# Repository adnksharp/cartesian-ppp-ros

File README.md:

# Cartesian Robot (PPP) ROS2

Robot cartesiano de 3 DOF con ROS2,

## Software y Hardware

<details>
    <summary>Software</summary>

* [ROS2 Jazzy](https://index.ros.org/p/desktop_full/#jazzy)
* [Gazebo Harmonic](https://gazebosim.org/docs/harmonic/getstarted/)
* [uROS Jazzy](https://github.com/micro-ROS/micro_ros_setup/tree/jazzy)
* [uROS Arduino Jazzy](https://github.com/micro-ROS/micro_ros_arduino/tree/jazzy)
* [KiCad](https://www.kicad.org)

</details>

<details>
    <summary>Componentes electrónicos</summary>

* 1 [ESP32 S3 WROOM 1 N16R8 DevKit](https://www.amazon.com/HiLetgo-ESP32-S3-ESP32-S3-DevKit-Bluetooth-Development/dp/B0CDWXWXCG)
* 2 [Módulos controladores de motores L298N](https://www.amazon.com/WWZMDiB-L298N-H-Bridge-Controller-Raspberry/dp/B0CR6BX5QL)
* 3 [Motores con encoder JGA25-371](https://www.amazon.com/JGA25-371-Encoder-Mounting-Bracket-Reduction/dp/B0CGLSGSZ7)
* 4 [LEDs 5730](https://www.amazon.com/AEDIKO-Lighting-Electronics-Components-Emitting/dp/B09XB5KDWS)
* 4 [Resistencias 220 Ohms 1206](https://www.amazon.com/Chanzon-Resistor-Tolerance-Resistors-Certificated/dp/B08R8CW7TX)
* 1 Fuente de alimentación 12V 2A

</details>

<details>
    <summary>Componentes mecánicos</summary>

* 12 perfiles de aluminio de 45x45x300 mm.
* 16 ángulos de aluminio de 45x45 mm.
* 3 tuercas de latón T8.
* 3 tornillos sin fin de 8x300 mm.
* 3 varillas lisas de 8x300 mm.
* 3 rodamientos SC8UU.
* 3 acopladores flexibles de 5x8 mm.
* 5 chumaceras KP08.
* 6 soportes SK8.
* Piezas impresas en 3D.

</details>

## Instalación
Para instalar el software de ROS2 Jazzy, se recomienda seguir la guía oficial de instalación de [ROS2](https://docs.ros.org/en/jazzy/Installation/Ubuntu-Install-Debs.html), el siguiente script instala el software de ROS2, Gazebo sim y micro-ROS en Ubuntu:

```shell
$SHELL ./src/install-ros.sh
```

Más información sobre el script en [src](src).

## Espacio de Trabajo de ROS2
Dentro de la carpeta ros-ws se encuentra el paquete en desarrollo `carobot`, el cual contiene los archivos para la visualización y simulación del robot cartesiano en Gazebo y RViz.

### Construcción del espacio de trabajo

```shell
cd ros-ws
colcon build
```

### Ejecución del lanzador

```shell
source install/setup.$(echo $SHELL | awk -F '/' '{print $NF}')
ros2 launch carobot display.launch.py
```

### Ejecución de la interfaz de usuario

```shell
source install/setup.$(echo $SHELL | awk -F '/' '{print $NF}')
ros2 run carobot pos_put.py
```

[ros-ws](ros-ws) contiene más información sobre el espacio de trabajo de ROS2.

## Electrónica

[electronic](electronic) contiene el diseño de la PCB del robot cartesiano en formato KiCad, el cual incluye el diseño de la PCB y el esquema eléctrico.

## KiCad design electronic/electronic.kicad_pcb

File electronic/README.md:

# Esquema elctrónico

El proyecto se desarrolló usando [KiCAD](https://www.kicad.org/). ([electronic.kicad_pro](electronic.kicad_pro)) se desarrollo para conectar una placa de ESP32 con 2 controladores de motores L298 y encoders de 3 motores JGA25-371. Los componentes utilizados en el proyecto son:

* 1 **ESP32 S3** WROOM 1 N16R8 DevKit
* 2 Modulos controladores de motores **L298**
* 3 Motores con encoder **JGA25-371**
* 4 LEDs
* 4 Resistencias **220 $\Omega$**
* 1 Fuente de alimentación **12V 2A**

## Esquema

El esquema eléctrico se encuentra dividido en ocho partes:

* 1 Alimentación: En esta sección se encuentra el conector de la fuente de alimentación para el circuito.
* 3 Motores
* 1 LED: LEDS conectados a los pines GPIO del microcontrolador y resistencias de 220 $\Omega$.
* 2 Controladores de motores
* 1 Microcontrolador

### Motores
En esta sección se encuentran los motores con encoder **JGA25-371**. 

* Las etiquetas del encoder se conectan a los pines GPIO del microcontrolador.
* Las etiquetas de alimentación se conectan a la salida de 3.3V del microcontrolador.
* Las etiquetas de los motores se conectan a los controladores de motores.

### Controladores de motores
En esta sección se encuentran los módulos de controladores de motores **L298N**. 

* Las etiquetas de los pines de control de los módulos se conectan a los pines GPIO del microcontrolador.
* Las etiquetas de alimentación se conectan a la fuente de alimentación y la salida de 5V de los controladores a la alimentación del microcontrolador.
* Las etiquetas de los motores se conectan a los motores.

### Microcontrolador
En esta sección se encuentra el microcontrolador **ESP32 S3** y las etiquetas de los pines que se utilizan para la comunicación con el resto de los componentes.

## PCB

La PCB fue diseñada para conectar todos los componentes del circuito. La PCB tiene un tamaño de 68.5x75 mm y fue diseñada para ser fabricada en dos capas. El diseño se encuentra en la carpeta `electronic` ([PCB.kicad_pcb](PCB.kicad_pcb)). Para la PCB se usan los siguientes componentes:

* 1 PCB de dos capas
* 1 Conector de alimentación **Barrel Jack**
* 2 Conectores **JST-B3B** para la alimentación de los controladores de motores.
* 3 Conectores **JST-B4B** para la conexión de los encoders de los motores.
* 2 Conectores **JST-B5B** para la conexión de los pines de control de los controladores de motores.
* 1 Terminal de 44 pines para la conexión del microcontrolador.
* 4 LEDs SMD **5730**
* 4 Resistencias 220 $\Omega$ SMD **1206**

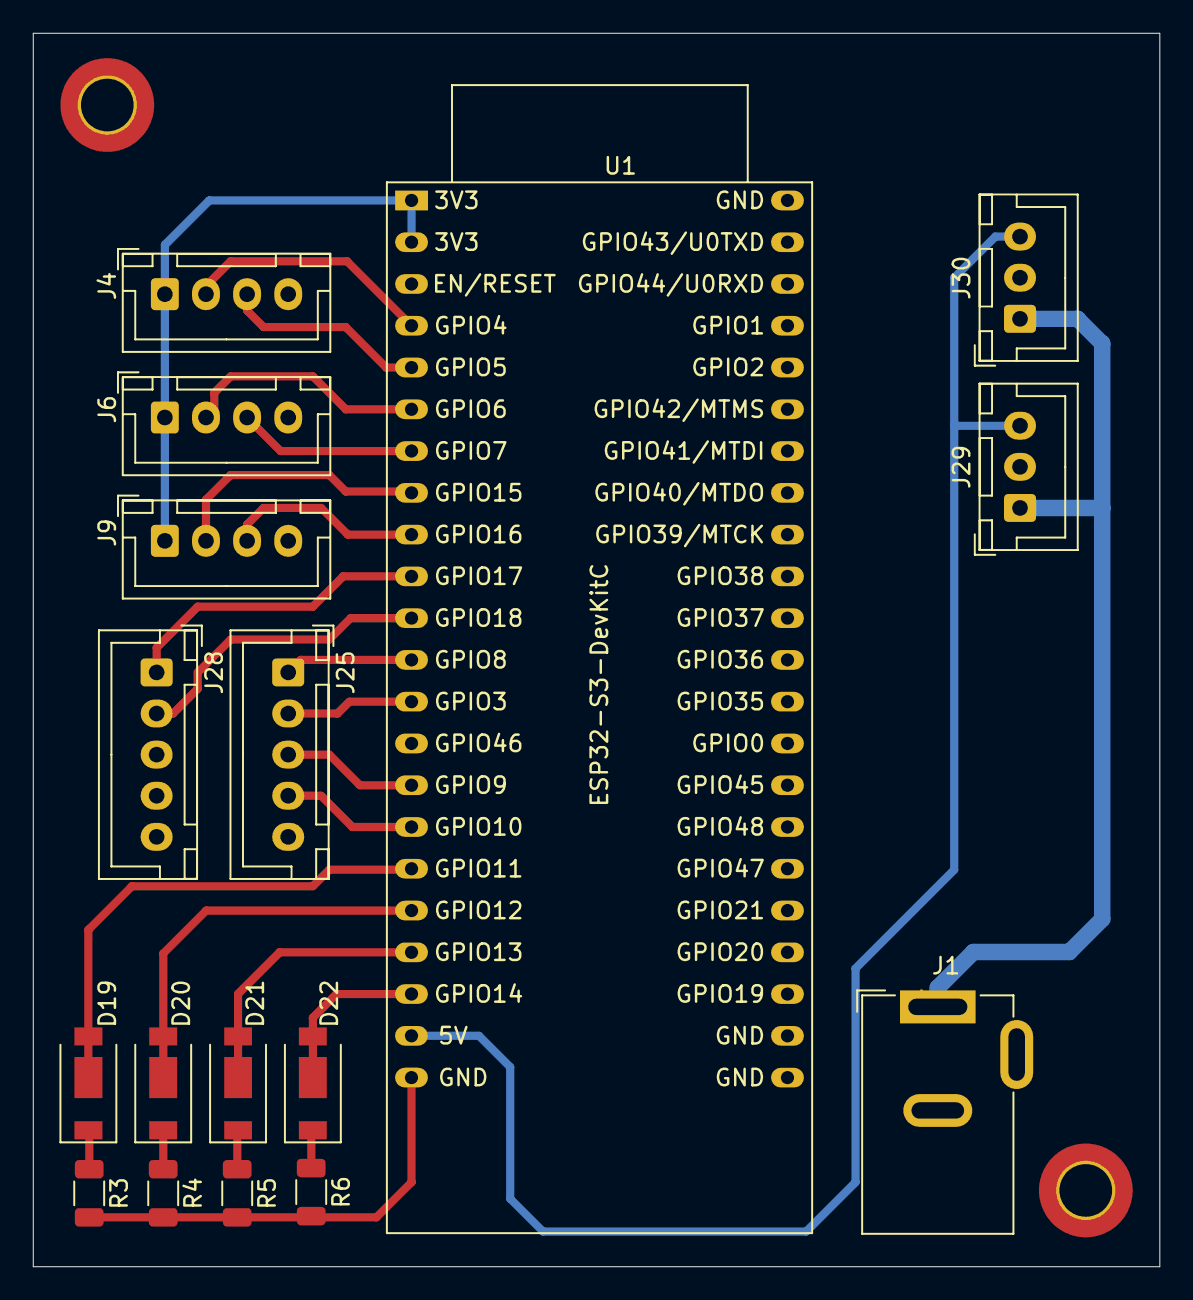
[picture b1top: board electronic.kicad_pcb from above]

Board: 2 copper layers, 68.5 x 75.0 mm, 17 parts (0 on the bottom side), 24 nets.

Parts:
D19, D20, D21, D22: LED; LED_Yuji_5730
J1: POWER SUPLY; BarrelJack_GCT_DCJ200-10-A_Horizontal
J4: ENC01; JST_XH_B4B-XH-A_1x04_P2.50mm_Vertical
J6: ENC02; JST_XH_B4B-XH-A_1x04_P2.50mm_Vertical
J9: ENC03; JST_XH_B4B-XH-A_1x04_P2.50mm_Vertical
J25, J28: Conn_01x05; JST_XH_B5B-XH-A_1x05_P2.50mm_Vertical
J29, J30: Screw_Terminal_01x03; JST_XH_B3B-XH-A_1x03_P2.50mm_Vertical
R3, R4, R5, R6: 220; R_1206_3216Metric
U1: ESP32-S3-DevKitC

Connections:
+3.3V: J4.1, J6.1, J9.1, U1.1 (3V3), U1.2 (3V3)
+5V: J29.3, J30.3, U1.21 (5V)
+12V: J1.1, J29.1, J30.1
DRVI101: J25.1, U1.12 (GPIO8/ADC1_CH7)
DRVI102: J28.1, U1.10 (GPIO17/ADC2_CH6)
DRVI201: J25.2, U1.13 (GPIO3/ADC1_CH2)
DRVI202: J28.2, U1.11 (GPIO18/ADC2_CH7)
DRVI301: J25.3, U1.15 (GPIO9/ADC1_CH8)
DRVI401: J25.4, U1.16 (GPIO10/ADC1_CH9)
Earth: J1.2, J4.4, J6.4, J9.4, J25.5, J28.5, J29.2, J30.2, R3.2, R4.2, R5.2, R6.2, U1.22 (GND), U1.23 (GND), U1.24 (GND), U1.44 (GND)
L_ENC_1: D19.2 (A), U1.17 (GPIO11/ADC2_CH0)
L_ENC_2: D20.2 (A), U1.18 (GPIO12/ADC2_CH1)
L_ENC_3: D21.2 (A), U1.19 (GPIO13/ADC2_CH2)
L_ROS: D22.2 (A), U1.20 (GPIO14/ADC2_CH3)
unnamed: D19.1 (K), R3.1
unnamed: D20.1 (K), R4.1
unnamed: D21.1 (K), R5.1
unnamed: D22.1 (K), R6.1
PH_A01: J4.2, U1.4 (GPIO4/ADC1_CH3)
PH_A02: J6.2, U1.6 (GPIO6/ADC1_CH5)
PH_A03: J9.2, U1.8 (GPIO15/ADC2_CH4/32K_P)
PH_B01: J4.3, U1.5 (GPIO5/ADC1_CH4)
PH_B02: J6.3, U1.7 (GPIO7/ADC1_CH6)
PH_B03: J9.3, U1.9 (GPIO16/ADC2_CH5/32K_N)

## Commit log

2025-03-03 chore: ros workspace init
2025-03-03 chore: ros workspace added to .gitignore
2025-03-10 chore: .gitignore updated
2025-03-13 test: uROS encoder publish topics
2025-03-13 chore: JGA MOTORS and L298N drivers added to KiCadschematic
2025-03-13 chore: pcd made
2025-03-13 chore: PCB updated
2025-03-13 chore: gerbar and images added
2025-03-13 chore: M3 hole added to PCB
2025-03-13 chore: images updated
2025-03-13 chore: gerber updated
2025-03-13 chore: 3d files updated
2025-03-14 chore: missing 3D models added to PCB
2025-03-14 chore: 3D model of L298N driver module added to the project
2025-03-14 chore: STL and STEP PCB files updated
2025-03-15 refactor: src dir changed
2025-03-15 chore: PCB Lite design added to the project
2025-03-18 docs: update README.md
2025-03-22 refactor (electronic): update PCB design
2025-03-24 chore (PCB 3D.png): update img files
2025-03-24 feat(ros-ws): start urdf project, publish robot with ROS2 and gazebo
2025-03-24 refactor(aunch/gazebo.launch.py): delete model path
2025-03-25 style(model.urdf): add colors to links
2025-03-28 chore(carobot): rename *_*.STL files to *.STL and add launcher for display the project in rviz2
2025-03-31 fix(model.urdf): coorect position and limit of joints and links in the model
2025-03-31 Revert "fix(model.urdf): coorect position and limit of joints and links in the model"
    This reverts commit 3ffb0695d2ab54cb5759cbb24cd0175b31b29e9f.
2025-03-31 Reapply "fix(model.urdf): coorect position and limit of joints and links in the model"
    This reverts commit d187cfb64390a7ce33d66d2385a874b4d395dfab.
2025-03-31 fix(model.urdf): correct position and limit of joints and links in the model
2025-03-31 fix(display.launch.py): add gui options for /opt/ros/jazzy/share/urdf_launch/launch/display.launch.py modified script
2025-04-05 feat(ros-ws/carobot): publish joint status from ROS2 (joint_state_publisher_gui) to gz by ros_gz_bridge
2025-04-06 fix(model.urdf): correct some definitions
2025-04-06 chore(model.urdf): test pid configurations
2025-04-06 refactor (img): update images
2025-04-07 chore(ros-ws): edit model.urdf
2025-04-09 refactor(ros-ws): update joint_state publisher based in data of gz sim
2025-04-11 refactor(ros-ws): change the filename attrib in urdf to use relative directory based on the project
2025-04-15 chore(stl): update STL files for the new design
2025-04-16 fix(model.urdf): update meshes and limits for new stl files
2025-04-16 chore (img): add Gazebo and RViz2 screenshots
2025-04-16 refactor(src): add scripts for install ROS2 and Gazebo sim
2025-04-16 chore(src): uncomment commands on install scripts
2025-04-17 feat(install-ros.sh): add micro-ROS install commands
2025-04-17 docs (README.md): update markdown files
2025-04-18 chore(electronic): update kicad files
2025-04-20 fix(carobot): update model
2025-04-29 test (yamanaka): test hardwary with arduino
2025-05-02 feat(ino/robot): init uROS publishers
2025-05-02 feat(ino/robot): add struct to control leds
2025-05-05 feat(ino/robot): add uROS subscribers
2025-05-09 feat(rosui): init user interface with neutralino.js and rclnodejs
2025-05-09 feat(rosui): add binaries
2025-05-16 test (yamanaka): init PID testings
2025-05-16 test (yamanaka): config PID by mm positions
2025-05-19 fix (yamanaka): tune pulse configs
2025-05-19 feat(robot): link PID control with the GUI by ROS2
2025-05-19 refactor(robot): restructures ROS2
2025-05-19 chore(yamanaka): replace spaces with tabs
